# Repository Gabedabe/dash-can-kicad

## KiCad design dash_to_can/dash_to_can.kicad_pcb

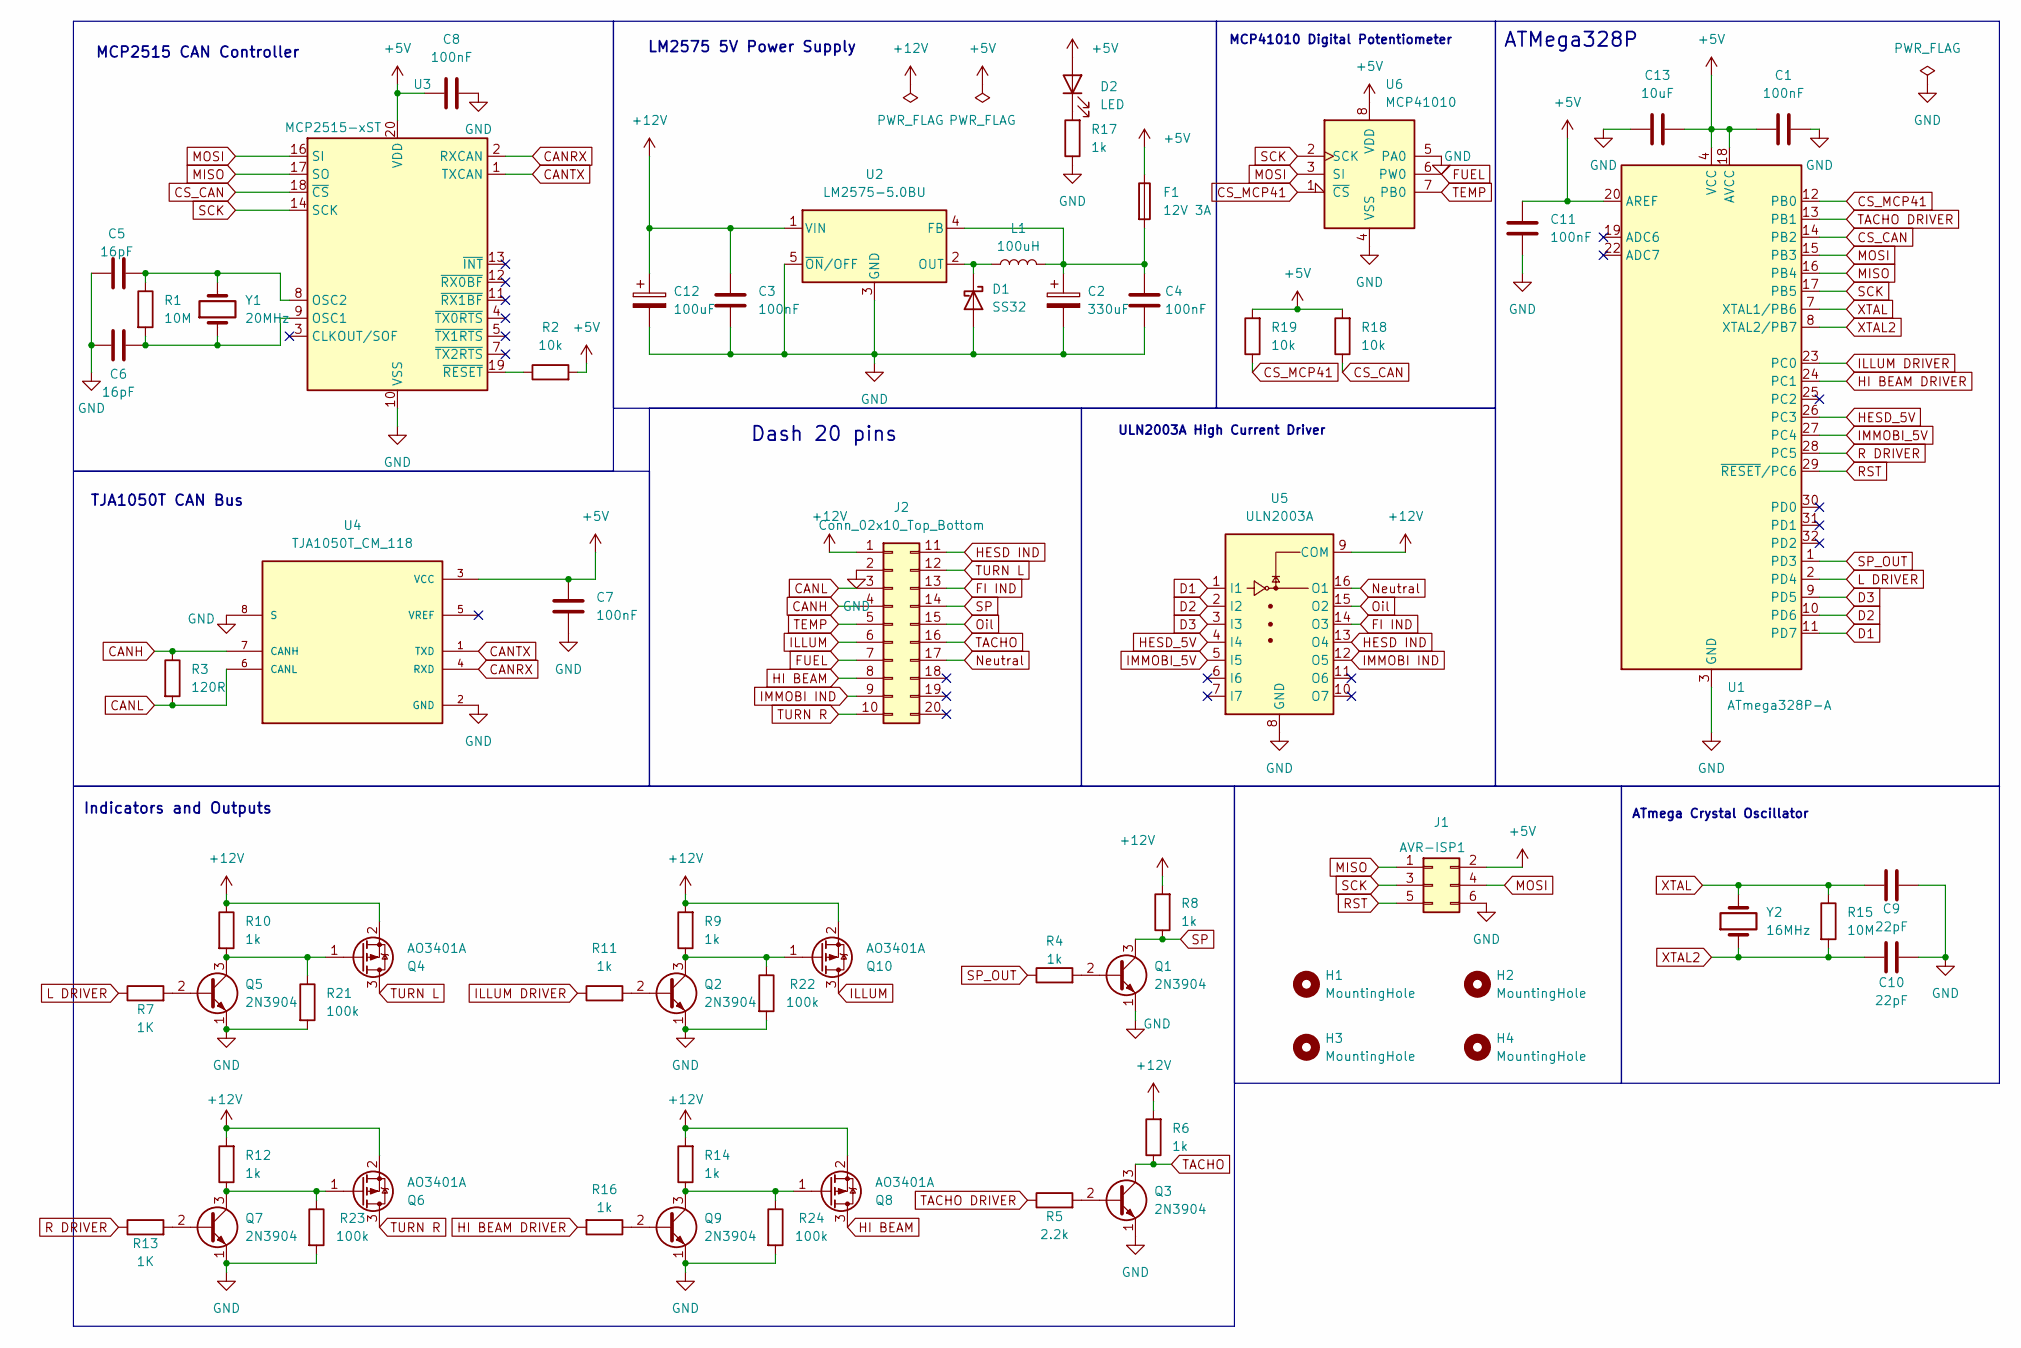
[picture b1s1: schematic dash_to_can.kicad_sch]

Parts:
C1, C3, C4, C7, C8, C11: 100nF; C_0805_2012Metric_Pad1.18x1.45mm_HandSolder
C2: 330uF; CP_Radial_D6.3mm_P2.50mm
C5, C6: 16pF; C_0805_2012Metric_Pad1.18x1.45mm_HandSolder
C9, C10: 22pF; C_0805_2012Metric_Pad1.18x1.45mm_HandSolder
C12: 100uF; CP_Radial_D6.3mm_P2.50mm
C13: 10uF; C_0805_2012Metric_Pad1.18x1.45mm_HandSolder
D1: SS32; D_SMA_Handsoldering
D2: LED; D_0805_2012Metric_Pad1.15x1.40mm_HandSolder
F1: 12V 3A; Fuse_0805_2012Metric_Pad1.15x1.40mm_HandSolder
H1, H2, H3, H4: MountingHole; MountingHole_3.2mm_M3
J1: AVR-ISP1; PinHeader_2x03_P2.54mm_Vertical
J2: Conn_02x10_Top_Bottom; PinHeader_2x10_P2.54mm_Vertical
L1: 100uH; L_TDK_SLF12575
Q1, Q2, Q3, Q5, Q7, Q9: 2N3904; SOT-23
Q4, Q6, Q8, Q10: AO3401A; SOT-23
R1, R15: 10M; R_0805_2012Metric_Pad1.20x1.40mm_HandSolder
R2, R18, R19: 10k; R_0805_2012Metric_Pad1.20x1.40mm_HandSolder
R3: 120R; R_0805_2012Metric_Pad1.20x1.40mm_HandSolder
R4, R6, R8, R9, R10, R11, R12, R14, R16, R17: 1k; R_0805_2012Metric_Pad1.20x1.40mm_HandSolder
R5: 2.2k; R_0805_2012Metric_Pad1.20x1.40mm_HandSolder
R7, R13: 1K; R_0805_2012Metric_Pad1.20x1.40mm_HandSolder
R21, R22, R23, R24: 100k; R_0805_2012Metric_Pad1.20x1.40mm_HandSolder
U1: ATmega328P-A; TQFP-32_7x7mm_P0.8mm
U2: LM2575-5.0BU; TO-263-5_TabPin3
U3: MCP2515-xST; TSSOP-20_4.4x6.5mm_P0.65mm
U4: TJA1050T_CM_118; SOIC-8_3.9x4.9mm_P1.27mm; PARTREV 4
U5: ULN2003A; SOIC-16_3.9x9.9mm_P1.27mm
U6: MCP41010; SOIC-8_3.9x4.9mm_P1.27mm
Y1: 20MHz; Crystal_HC49-4H_Vertical
Y2: 16MHz; Crystal_HC49-4H_Vertical

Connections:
+5V: C1.1, C7.2, C8.1, C11.2, C13.1, D2.2 (A), F1.1, J1.2, R2.2, R18.2, R19.2, U1.4 (VCC), U1.6 (VCC), U1.18 (AVCC), U1.20 (AREF), U3.20 (VDD), U4.3 (VCC), U6.8 (VDD)
+12V: C3.1, C12.1, J2.1, Q4.2 (S), Q6.2 (S), Q8.2 (S), Q10.2 (S), R6.2, R8.2, R9.2, R10.1, R12.2, R14.2, U2.1 (VIN), U5.9 (COM)
CANH: J2.4, R3.1, U4.7 (CANH)
CANL: J2.3, R3.2, U4.6 (CANL)
CANRX: U3.2 (RXCAN), U4.4 (RXD)
CANTX: U3.1 (TXCAN), U4.1 (TXD)
CS_CAN: R18.1, U1.14 (PB2), U3.18 (~CS)
CS_MCP41: R19.1, U1.12 (PB0), U6.1 (~CS)
D1: U1.11 (PD7), U5.1 (I1)
D2: U1.10 (PD6), U5.2 (I2)
D3: U1.9 (PD5), U5.3 (I3)
FI IND: J2.13, U5.14 (O3)
FUEL: J2.7, U6.6 (PW0)
GND: C1.2, C2.2, C3.2, C4.2, C5.1, C6.1, C7.1, C8.2, C9.2, C10.2, C11.1, C12.2, C13.2, D1.2 (A), J1.6, J2.2, Q1.1 (E), Q2.1 (E), Q3.1 (E), Q5.1 (E), Q7.1 (E), Q9.1 (E), R17.1, R21.2, R22.2, R23.2, R24.2, U1.3 (GND), U1.5 (GND), U1.21 (GND), U2.3 (GND), U2.5 (~ON/OFF), U3.10 (VSS), U4.2 (GND), U4.8 (S), U5.8 (GND), U6.4 (VSS), U6.5 (PA0)
HESD IND: J2.11, U5.13 (O4)
HESD_5V: U1.26 (PC3), U5.4 (I4)
HI BEAM: J2.8, Q8.3 (D)
HI BEAM DRIVER: R16.2, U1.24 (PC1)
ILLUM: J2.6, Q10.3 (D)
ILLUM DRIVER: R11.1, U1.23 (PC0)
IMMOBI IND: J2.9, U5.12 (O5)
IMMOBI_5V: U1.27 (PC4), U5.5 (I5)
L DRIVER: R7.1, U1.2 (PD4)
MISO: J1.1, U1.16 (PB4), U3.17 (SO)
MOSI: J1.4, U1.15 (PB3), U3.16 (SI), U6.3 (SI)
unnamed: D1.1 (K), L1.1, U2.2 (OUT)
unnamed: D2.1 (K), R17.2
unnamed: Q1.2 (B), R4.2
unnamed: Q2.2 (B), R11.2
unnamed: Q3.2 (B), R5.2
unnamed: Q4.1 (G), Q5.3 (C), R10.2, R21.1
unnamed: Q5.2 (B), R7.2
unnamed: Q6.1 (G), Q7.3 (C), R12.1, R23.1
unnamed: Q7.2 (B), R13.2
unnamed: Q8.1 (G), Q9.3 (C), R14.1, R24.1
unnamed: Q9.2 (B), R16.1
unnamed: Q2.3 (C), Q10.1 (G), R9.1, R22.1
unnamed: C2.1, C4.1, F1.2, L1.2, U2.4 (FB)
unnamed: C6.2, R1.2, U3.9 (OSC1), Y1.1
unnamed: C5.2, R1.1, U3.8 (OSC2), Y1.2
unnamed: R2.1, U3.19 (~RESET)
Neutral: J2.17, U5.16 (O1)
Oil: J2.15, U5.15 (O2)
R DRIVER: R13.1, U1.28 (PC5)
RST: J1.5, U1.29 (~RESET/PC6)
SCK: J1.3, U1.17 (PB5), U3.14 (SCK), U6.2 (SCK)
SP: J2.14, Q1.3 (C), R8.1
SP_OUT: R4.1, U1.1 (PD3)
TACHO: J2.16, Q3.3 (C), R6.1
TACHO DRIVER: R5.1, U1.13 (PB1)
TEMP: J2.5, U6.7 (PB0)
TURN L: J2.12, Q4.3 (D)
TURN R: J2.10, Q6.3 (D)
XTAL: C9.1, R15.1, U1.7 (XTAL1/PB6), Y2.2
XTAL2: C10.1, R15.2, U1.8 (XTAL2/PB7), Y2.1

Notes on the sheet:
Dash 20 pins
MCP41010 Digital Potentiometer
Indicators and Outputs
LM2575 5V Power Supply
ATMega328P
ULN2003A High Current Driver
MCP2515 CAN Controller
ATmega Crystal Oscillator
TJA1050T CAN Bus

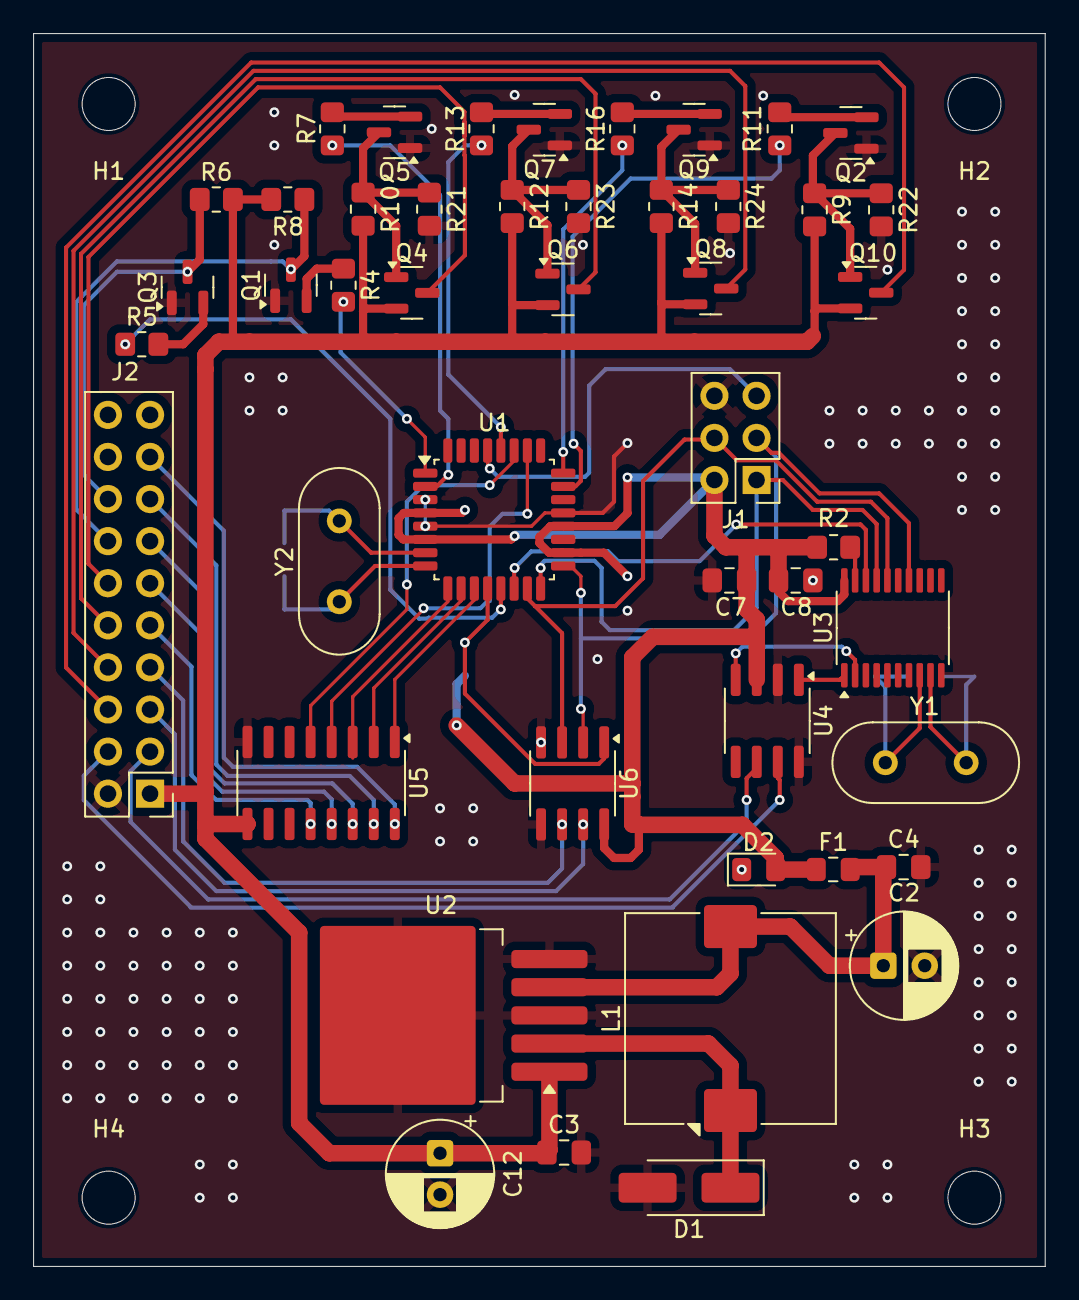
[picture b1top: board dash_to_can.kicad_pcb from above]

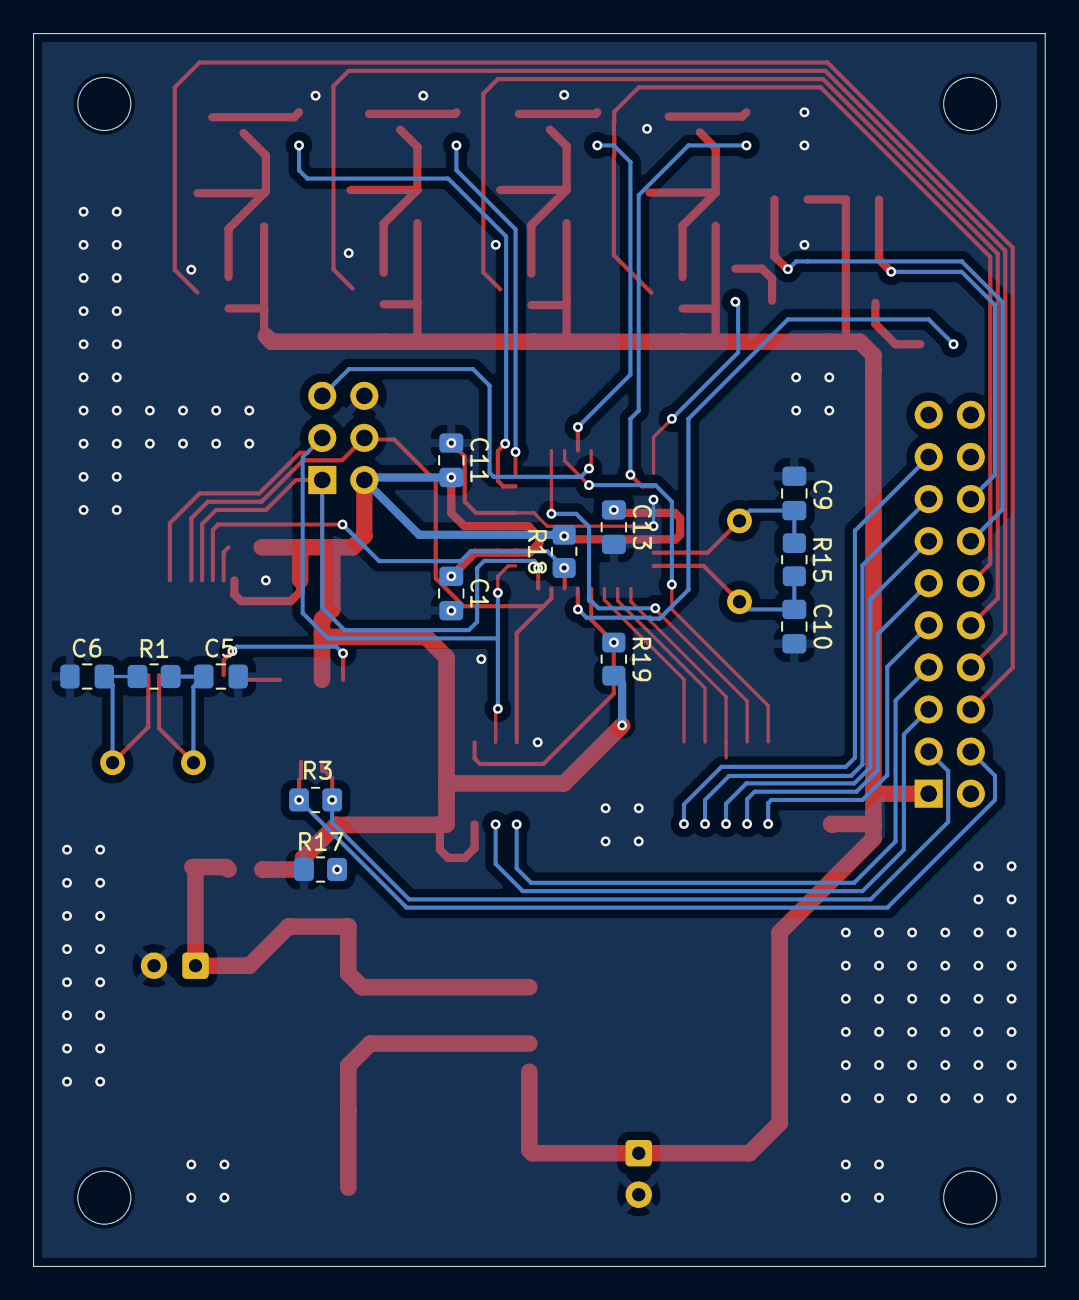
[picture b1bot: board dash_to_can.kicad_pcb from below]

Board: 2 copper layers, 61.1 x 74.4 mm, 64 parts (13 on the bottom side), 55 nets.

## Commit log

2026-02-26 first upload
2026-03-02 updated update
2026-03-03 Uploading my (Gabriel's) changes
    Tweaking and organising schematic
2026-03-11 PCB update, still wiring to do
2026-03-11 Fixing footprints official
2026-03-14 Second Draft
2026-03-16 3rd Draft with Nicholas advice
